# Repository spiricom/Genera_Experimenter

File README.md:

# Genera_H7_rev3
Genera repository for the rev3 boards (summer 2019) STM32H743
test

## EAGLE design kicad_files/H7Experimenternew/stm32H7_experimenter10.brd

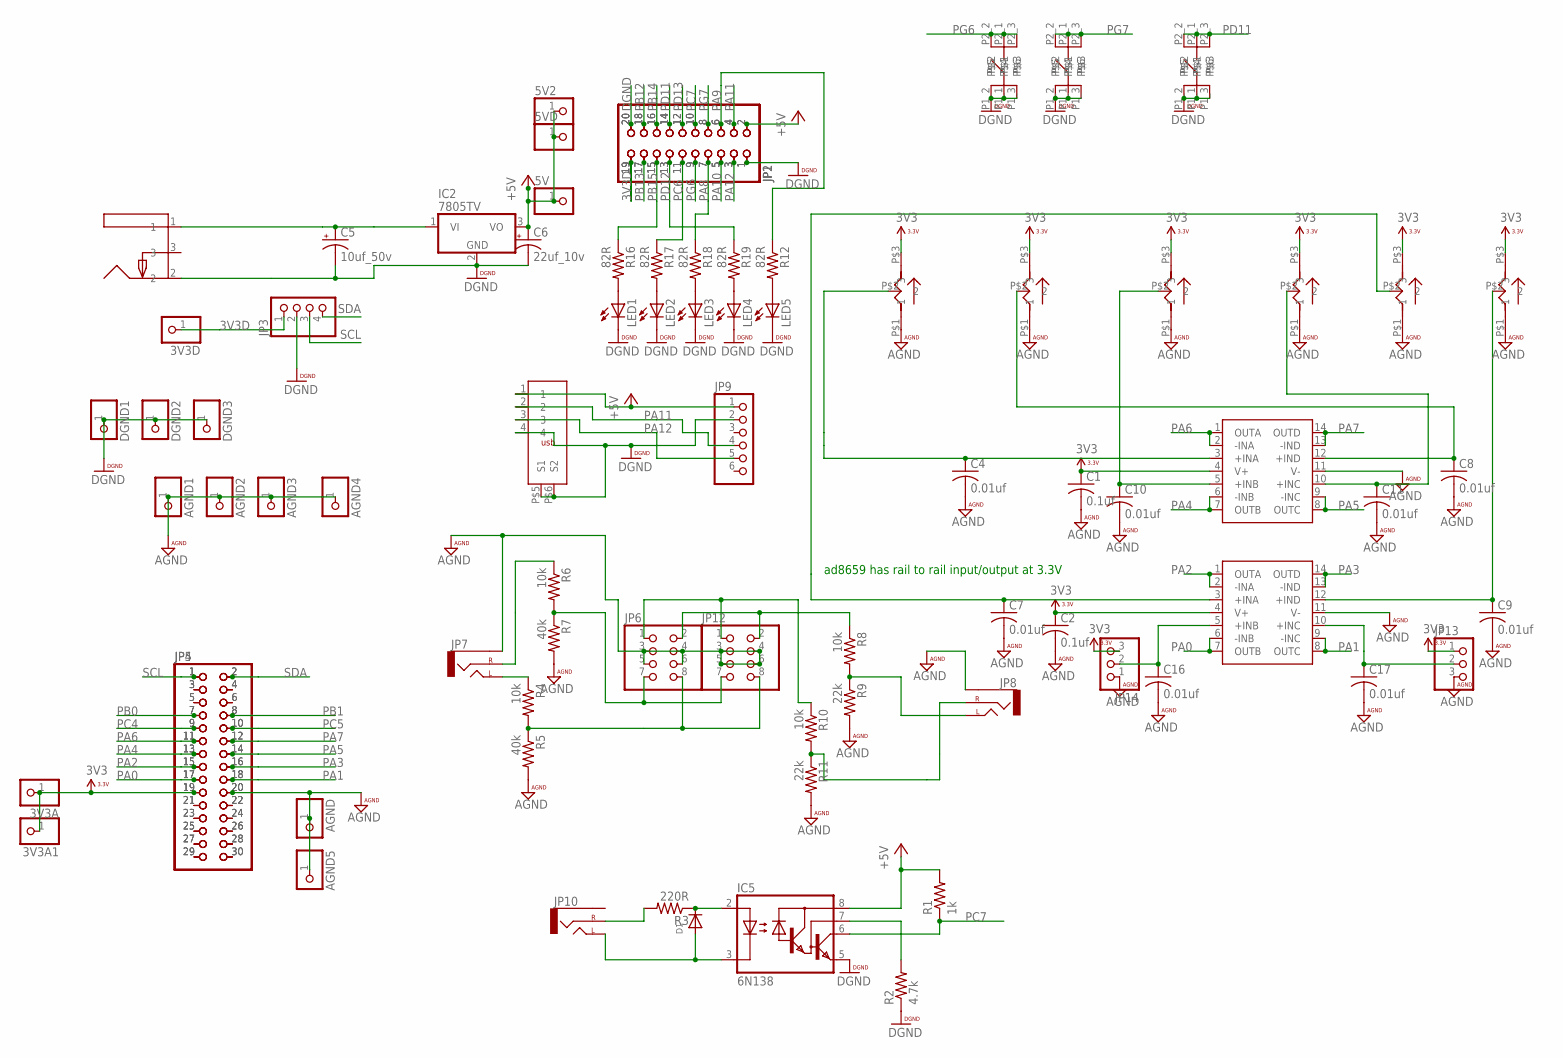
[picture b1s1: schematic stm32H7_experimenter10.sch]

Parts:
3V3A, 3V3A1, 3V3D, 5V, 5V2, 5VD: PINHD-1X1; 1X01; PARTNO *DNP
AGND, AGND1, AGND2, AGND3, AGND4, AGND5: PINHD-1X1; 1X01; PARTNO *DNP
C1, C2: 0.1uf; C025-030X050; PARTNO K104K15X7RF5TL2
C4, C7, C8, C9, C10, C11, C16, C17: 0.01uf; C025-030X050; PARTNO K103K15X7RF5TL2
C5: 10uf_50v; SMC_C; PARTNO 293D106X9035C2TE3
C6: 22uf_10v; SMC_C; PARTNO T491C226K016AT
D1: DIODEDO-1N4148; DO-1N4148; PARTNO 1N4148
DGND1, DGND2, DGND3: PINHD-1X1; 1X01; PARTNO *DNP
IC1, IC3: AD8659; SO14; PARTNO AD8659ARZ-R7
IC2: 7805TV; TO220V; PARTNO VX7805-1000
IC5: 6N138; DIL08; PARTNO 6N138
JP1: PINHD-2X10; 2X10; PARTNO *DNP
JP2: PINHD-2X10; 2X10; PARTNO 67996-120HLF
JP3: PINHD-1X4; 1X04; PARTNO *DNP
JP4: PINHD-2X15; 2X15; PARTNO 67996-130HLF
JP5: PINHD-2X15; 2X15; PARTNO *DNP
JP6: PINHD-2X4; 2X04; PARTNO 67996-108HLF
JP7, JP8, JP10: AUDIO-JACKPTH; AUDIO-JACK; PARTNO SJ1-3525N
JP9: PINHD-1X6; 1X06
JP12: PINHD-2X4; 2X04; PARTNO *DNP
JP13, JP14: PINHD-1X3; 1X03; PARTNO *DNP
LED1, LED2, LED3, LED4, LED5: LED3MM; PARTNO 151031SS04000
P1, P2, P3, P4, P5, P6: RK09SONGHUEI; R0904N; PARTNO *
R1: 1k; 0204/5; PARTNO RNMF14FTC1K00
R2: 4.7k; 0204/5; PARTNO RNMF14FTC4K70
R3: 220R; 0204/5; PARTNO RNMF14FTC220R
R4, R6, R8, R10: 10k; 0204/5; PARTNO RNMF14FTC10K0
R5, R7: 40k; 0204/5; PARTNO RNMF14FTC39K0
R9, R11: 22k; 0204/5; PARTNO RNMF14FTC22K0
R12, R18, R19: 82R; 0204/5; PARTNO RNMF14FTC82R0
R16, R17: 82R; 0204V; PARTNO RNMF14FTC82R0
S1, S2, S3: TL52_PLUS; PARTNO TL52AF160Q
U$1: PJ-058AH_PWR_JACK; PJ-058AH
U$3: USB_292303-1; 292303

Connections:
3V3A: 3V3A.1, 3V3A1.1, C1.1, C2.1, IC1.4 (V+), IC3.4 (V+), JP4.19, JP5.19, JP13.1, JP14.3, P1.P$3 (3), P2.P$3 (3), P3.P$3 (3), P4.P$3 (3), P5.P$3 (3), P6.P$3 (3)
3V3D: 3V3D.1, JP1.19, JP2.19, JP3.1
+5V: 5V.1, 5V2.1, 5VD.1, C6.+, IC2.3 (VO), IC5.8 (VCC), JP1.2, JP2.2, JP9.1, R1.2, U$3.1
AGND: AGND.1, AGND1.1, AGND2.1, AGND3.1, AGND4.1, AGND5.1, C1.2, C2.2, C4.2, C7.2, C8.2, C9.2, C10.2, C11.2, C16.2, C17.2, IC1.11 (V-), IC3.11 (V-), JP4.20, JP5.20, JP6.3, JP6.4, JP6.5, JP6.6, JP7.SLEEVE, JP8.SLEEVE, JP12.3, JP12.4, JP12.5, JP12.6, JP13.3, JP14.1, P1.P$1 (1), P2.P$1 (1), P3.P$1 (1), P4.P$1 (1), P5.P$1 (1), P6.P$1 (1), R5.2, R7.2, R9.2, R11.2
DGND: C5.-, C6.-, DGND1.1, DGND2.1, DGND3.1, IC2.2 (GND), IC5.5 (GND), JP1.1, JP1.20, JP2.1, JP2.20, JP3.2, JP9.2, LED1.K (C), LED2.K (C), LED3.K (C), LED4.K (C), LED5.K (C), R2.1, S1.P1_1, S1.P1_2, S1.P1_3, S2.P1_1, S2.P1_2, S2.P1_3, S3.P1_1, S3.P1_2, S3.P1_3, U$1.2, U$3.4, U$3.P$5 (S1), U$3.P$6 (S2)
unnamed: D1.A, IC5.3 (C), JP10.TIP (LEFT)
unnamed: D1.C, IC5.2 (A), R3.1
unnamed: IC5.7 (VB), R2.2
unnamed: JP10.RING (RIGHT), R3.2
unnamed: C4.1, IC1.3 (+INA), P1.P$2 (2)
unnamed: C8.1, IC1.12 (+IND), P2.P$2 (2)
unnamed: C10.1, IC1.5 (+INB), P3.P$2 (2)
unnamed: C11.1, IC1.10 (+INC), P4.P$2 (2)
unnamed: JP4.3, JP5.3
unnamed: JP4.4, JP5.4
unnamed: JP4.5, JP5.5
unnamed: JP4.6, JP5.6
unnamed: C7.1, IC3.3 (+INA), P5.P$2 (2)
unnamed: C9.1, IC3.12 (+IND), P6.P$2 (2)
unnamed: JP4.21, JP5.21
unnamed: JP4.22, JP5.22
unnamed: C5.+, IC2.1 (VI), U$1.1
unnamed: C16.1, IC3.5 (+INB), JP14.2
unnamed: JP6.8, JP12.8, R4.2, R5.1
unnamed: JP6.7, JP12.7, R6.2, R7.1
unnamed: LED5.A, R12.2
unnamed: JP7.TIP (LEFT), R4.1
unnamed: JP8.TIP (LEFT), R8.2, R9.1
unnamed: C17.1, IC3.10 (+INC), JP13.2
unnamed: JP7.RING (RIGHT), R6.1
unnamed: JP6.2, JP12.2, R8.1
unnamed: JP8.RING (RIGHT), R10.2, R11.1
unnamed: JP6.1, JP12.1, R10.1
unnamed: LED1.A, R16.2
unnamed: LED2.A, R17.2
unnamed: LED3.A, R18.2
unnamed: LED4.A, R19.2
unnamed: JP4.23, JP5.23
unnamed: JP4.24, JP5.24
unnamed: JP4.25, JP5.25
unnamed: JP4.26, JP5.26
unnamed: JP4.27, JP5.27
unnamed: JP4.28, JP5.28
unnamed: JP4.29, JP5.29
unnamed: JP4.30, JP5.30
PA0: IC3.6 (-INB), IC3.7 (OUTB), JP4.17, JP5.17
PA1: IC3.8 (OUTC), IC3.9 (-INC), JP4.18, JP5.18
PA2: IC3.1 (OUTA), IC3.2 (-INA), JP4.15, JP5.15
PA3: IC3.13 (-IND), IC3.14 (OUTD), JP4.16, JP5.16
PA4: IC1.6 (-INB), IC1.7 (OUTB), JP4.13, JP5.13
PA5: IC1.8 (OUTC), IC1.9 (-INC), JP4.14, JP5.14
PA6: IC1.1 (OUTA), IC1.2 (-INA), JP4.11, JP5.11
PA7: IC1.13 (-IND), IC1.14 (OUTD), JP4.12, JP5.12
PA8: JP1.7, JP2.7, R18.1
PA9: JP1.6, JP2.6, R12.1
PA10: JP1.5, JP2.5
PA11: JP1.4, JP2.4, JP9.4, U$3.2
PA12: JP1.3, JP2.3, JP9.5, U$3.3
PB0: JP4.7, JP5.7
PB1: JP4.8, JP5.8
PB12: JP1.18, JP2.18
PB13: JP1.17, JP2.17
PB14: JP1.16, JP2.16
PB15: JP1.15, JP2.15, R16.1
PC4: JP4.9, JP5.9
PC5: JP4.10, JP5.10
PC6: JP1.11, JP2.11, R17.1
PC7: IC5.6 (VO), JP1.10, JP2.10, R1.1
PD11: JP1.14, JP2.14, S3.P2_1, S3.P2_2, S3.P2_3
PD12: JP1.13, JP2.13, R19.1
PD13: JP1.12, JP2.12
PG6: JP1.9, JP2.9, S1.P2_1, S1.P2_2, S1.P2_3
PG7: JP1.8, JP2.8, S2.P2_1, S2.P2_2, S2.P2_3
SCL: JP3.3, JP4.1, JP5.1
SDA: JP3.4, JP4.2, JP5.2

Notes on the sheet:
ad8659 has rail to rail input/output at 3.3V

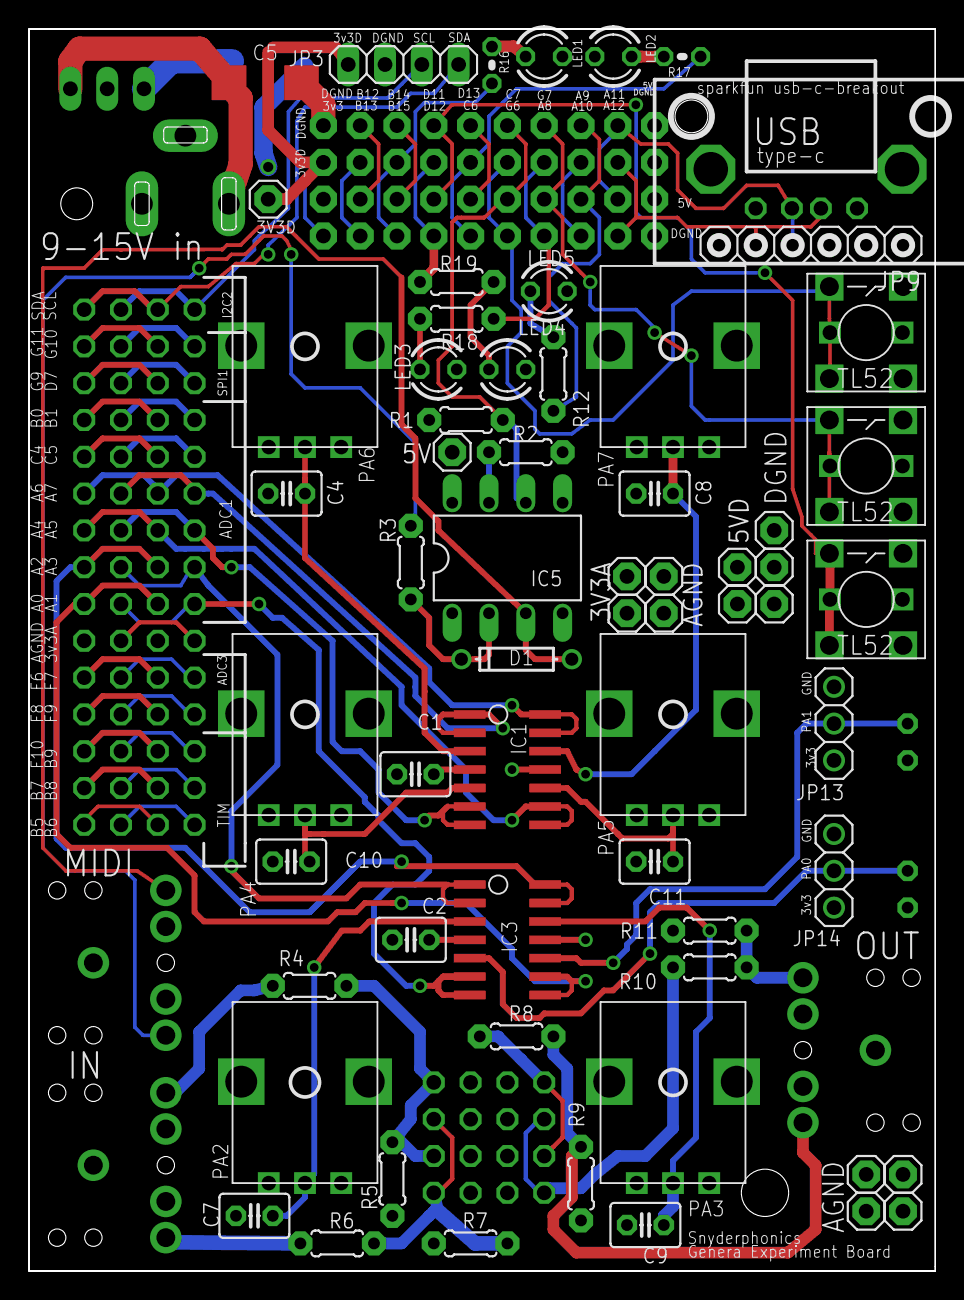
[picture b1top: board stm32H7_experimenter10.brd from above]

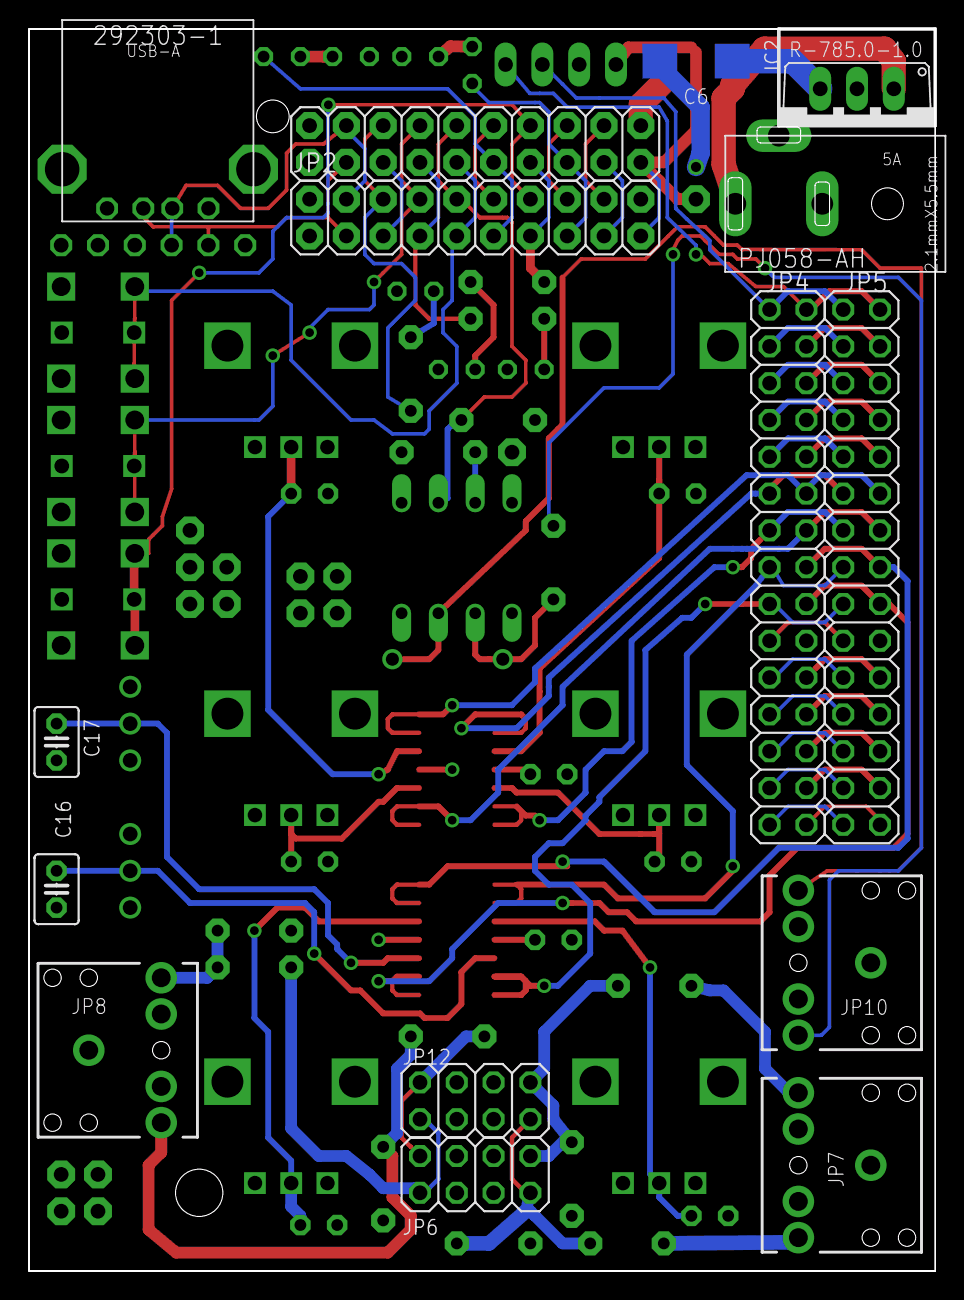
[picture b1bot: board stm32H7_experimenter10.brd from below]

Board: 6 copper layers, 62.5 x 85.7 mm, 77 parts (15 on the bottom side), 75 nets.

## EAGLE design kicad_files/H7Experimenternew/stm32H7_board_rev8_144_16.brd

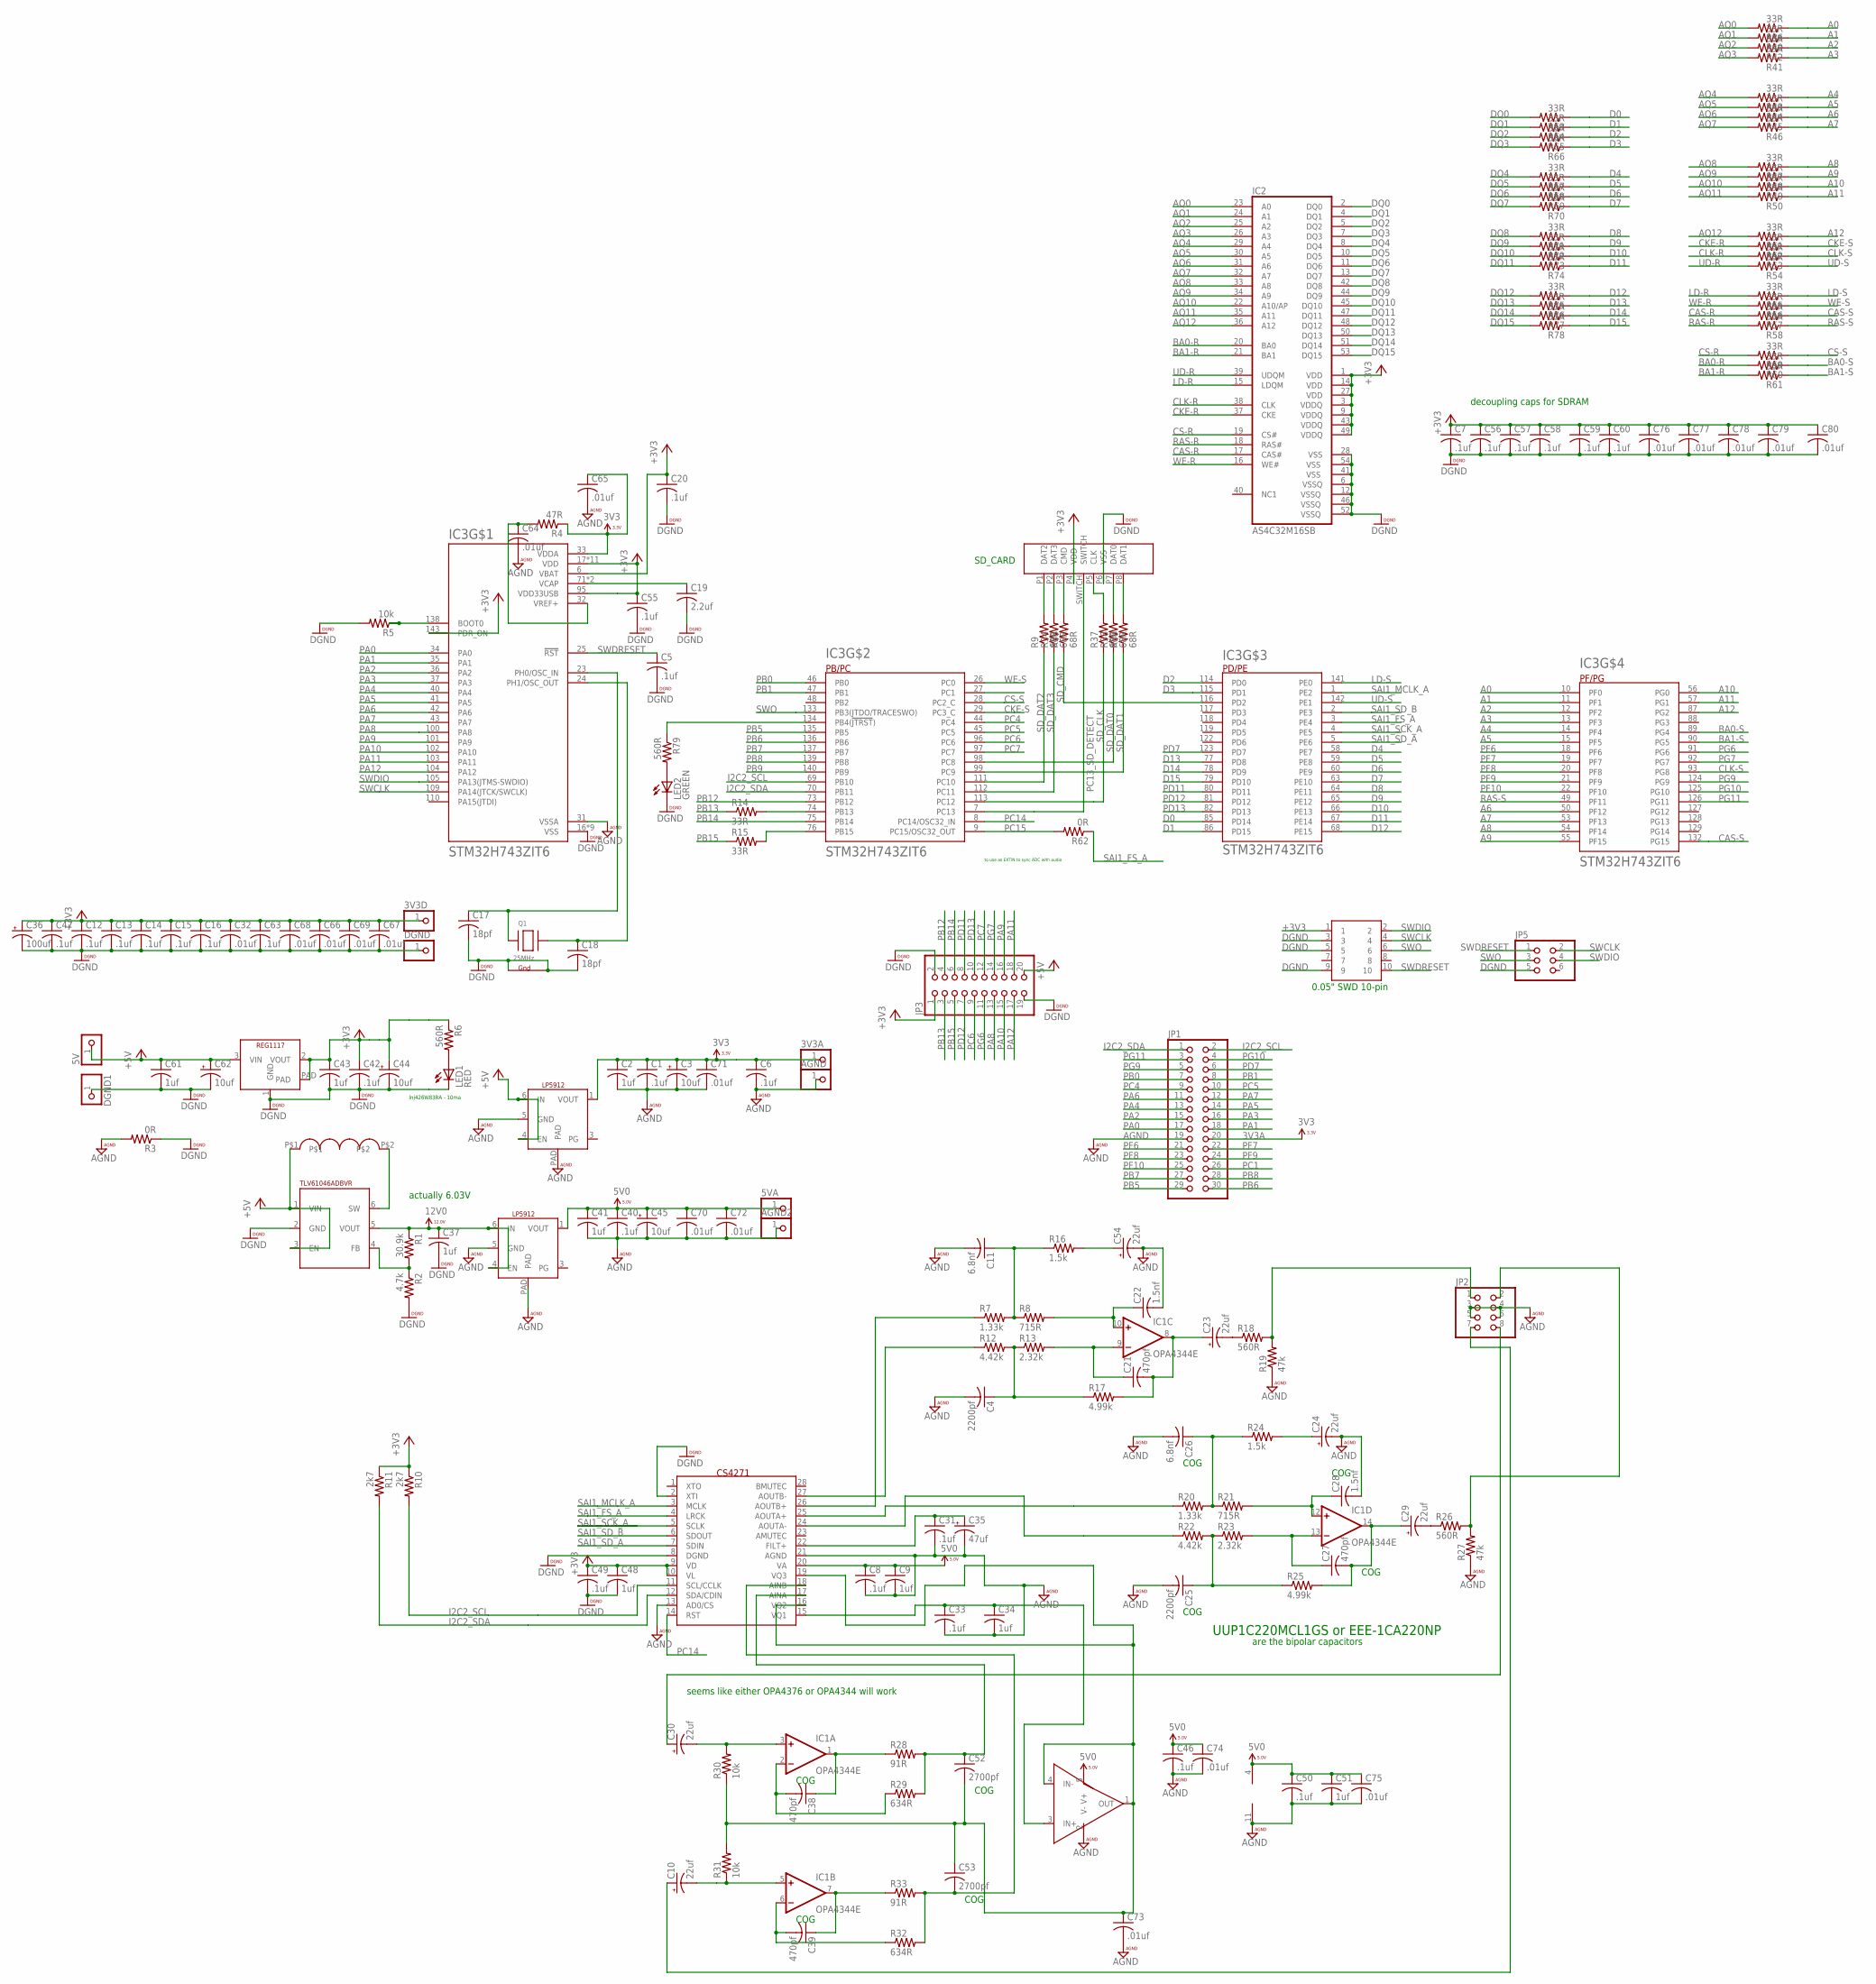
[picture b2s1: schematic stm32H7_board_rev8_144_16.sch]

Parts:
3V3A, 3V3D, 5V, 5VA: PINHD-1X1; 1X01; PARTNO *DNP
AGND, AGND2: PINHD-1X1; 1X01; PARTNO *DNP
C1, C8, C31, C33, C40, C42, C46, C49, C50: .1uf; C0603; PARTNO CC0603KRX7R8BB104
C2, C9, C34, C37, C41, C43, C48, C51, C61: 1uf; C1206; PARTNO C3216X7R1E105K085AA
C3, C44, C45, C62: 10uf; SMC_B; PARTNO TAJB106K025RNJ
C4, C25: 2200pf; C0603; PARTNO CC0603JRNPO9BN221
C5, C6, C7, C12, C13, C14, C15, C16, C20, C47, C55, C56, C57, C58, C59, C60, C63: .1uf; C0402; PARTNO CC0402KRX7R8BB104
C10, C23, C24, C29, C30, C54: 22uf; PANASONIC_D; PARTNO EEE-1CA220NP
C11, C26: 6.8nf; C0603; PARTNO C0603C682J5GACTU
C17, C18: 18pf; C0603; PARTNO CL10C180JB8NNNC
C19: 2.2uf; C1206; PARTNO T491A225K020AT
C21, C27, C38, C39: 470pf; C0603; PARTNO CC0603JRNPO9BN471
C22, C28: 1.5nf; C0603; PARTNO C0603C152J5GACTU
C32, C64, C65: .01uf; C0402; PARTNO CC0402KRX7R8BB103
C35: 47uf; PANASONIC_D; PARTNO EEE-1CA470AP
C36: 100uf; PANASONIC_E; PARTNO EEE-1CA101AP
C52, C53: 2700pf; C0603; PARTNO C0603C272J5GACTU
C66, C67, C68, C69, C70, C71, C72, C73, C74, C75, C76, C77, C78, C79, C80: .01uf; C0201; PARTNO TMK063B7103KP-F
DGND, DGND1: PINHD-1X1; 1X01; PARTNO *DNP
IC1: OPA4344E; TSSOP14; PARTNO ADA4807-4ARUZ-R7
IC2: AS4C32M16SB; TSOP54; PARTNO AS4C16M16SA-7TCN
IC3: STM32H743ZIT6; QFP50P2200X2200X160-144N; PARTNO STM32H743ZIT6
IC4: REG1117; SOT223; PARTNO LM1117IMPX-3.3/NOPB
IC5: CS4271; TSSOP28; PARTNO CS4271-CZZ
IC6: TLV170; SOT23-5L; PARTNO TLV170IDBVT
IC7: TLV61046ADBVR; SOT23-6; PARTNO TLV61046ADBVR
IC8: LP5912; 6-WSON; PARTNO LP5912-5.0DRVR
IC9: LP5912; 6-WSON; PARTNO LP5912-3.3DRVT
JP1: PINHD-2X15; 2X15; PARTNO 76342-315LF
JP2: PINHD-2X4; 2X04; PARTNO 76342-304LF
JP3: PINHD-2X10; 2X10; PARTNO 76342-310LF
JP5: PINHD-2X3; 2X03; PARTNO *DNP
L1: 74438336100; 1212; PARTNO 74438336100
LED1: RED; CHIP-LED0603; PARTNO 5973006507F
LED2: GREEN; CHIP-LED0603; PARTNO 5973506507F
Q1: 25MHz; NX3225; PARTNO 7M-25.000MAAJ-T
R1: 30.9k; R0603; PARTNO RT0603BRD0730K9L
R2: 4.7k; R0603; PARTNO CRCW06034K70FKEAHP
R3, R62: 0R; R0603; PARTNO RCS06030000Z0EA
R4: 47R; R0603; PARTNO ESR03EZPJ470
R5: 10k; R0402; PARTNO RC0402FR-0710KL
R6, R18, R26, R79: 560R; R0603; PARTNO ESR03EZPF5600
R7, R20: 1.33k; R0603; PARTNO RT0603BRD071K33L
R8, R21: 715R; R0603; PARTNO RC0603FR-07715RL
R9, R34, R35, R37, R38, R39: 68R; R0201; PARTNO RC0201FR-0768RL
R10, R11: 2k7; R0603; PARTNO RT0603BRD072K7L
R12, R22: 4.42k; R0603; PARTNO RT0603BRD074K42L
R13, R23: 2.32k; R0603; PARTNO RT0603BRD072K32L
R14, R15: 33R; R0402; PARTNO RC0402FR-0733RL
R16, R24: 1.5k; R0603; PARTNO ESR03EZPJ152
R17, R25: 4.99k; R0603; PARTNO RT0603BRD074K99L
R19, R27: 47k; R0603; PARTNO ESR03EZPJ473
R28, R33: 91R; R0603; PARTNO RC0603JR-0791RL
R29, R32: 634R; R0603; PARTNO RC0603FR-07634RL
R30, R31: 10k; R0603; PARTNO ESR03EZPF1002
R36, R40, R41, R42, R43, R44, R45, R46, R47, R48, R49, R50, R51, R52, R53, R54, R55, R56, R57, R58, R59, R60, R61, R63, R64, R65, R66, R67, R68, R69, R70, R71, R72, R73, R74, R75, R76, R77, R78: 33R; R0201; PARTNO RC0201FR-0733RL
X1: 1050270001_SD_CARD_CONNECTOR; 1050270001; PARTNO 1050270001
X2: 3221-10-0300-00; PARTNO 3221-10-0300-00

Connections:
3V3A: 3V3A.1, C1.1, C2.1, C3.+, C6.1, C65.1, C71.1, IC3.33 (VDDA), IC9.1 (VOUT), JP1.20, R4.1
5V0: 5VA.1, C8.1, C9.1, C40.1, C41.1, C45.+, C46.1, C50.1, C51.1, C70.1, C72.1, C74.1, C75.1, IC1.4 (V+), IC5.20 (VA), IC6.5 (V+), IC8.1 (VOUT)
12V0: C37.1, IC7.5 (VOUT), IC8.4 (EN), IC8.6 (IN), R1.1
+3V3: 3V3D.1, C7.1, C12.1, C13.1, C14.1, C15.1, C16.1, C20.1, C32.1, C36.+, C42.1, C43.1, C44.+, C47.1, C48.1, C49.1, C55.1, C56.1, C57.1, C58.1, C59.1, C60.1, C63.1, C66.1, C67.1, C68.1, C69.1, C76.1, C77.1, C78.1, C79.1, C80.1, IC2.1 (VDD), IC2.3 (VDDQ), IC2.9 (VDDQ), IC2.14 (VDD), IC2.27 (VDD), IC2.43 (VDDQ), IC2.49 (VDDQ), IC3.6 (VBAT), IC3.17 (VDD), IC3.30 (VDD), IC3.39 (VDD), IC3.52 (VDD), IC3.62 (VDD), IC3.72 (VDD), IC3.84 (VDD), IC3.95 (VDD33USB), IC3.108 (VDD), IC3.121 (VDD), IC3.131 (VDD), IC3.143 (PDR_ON), IC3.144 (VDD), IC4.2 (VOUT), IC4.PAD, IC5.9 (VD), IC5.10 (VL), JP3.1, R6.1, R10.1, R11.1, X1.P4 (VDD), X2.1
+5V: 5V.1, C61.1, C62.+, IC4.3 (VIN), IC7.1 (VIN), IC7.3 (EN), IC9.4 (EN), IC9.6 (IN), JP3.20, L1.P$1
A0: IC3.10 (PF0), R36.1
A1: IC3.11 (PF1), R40.1
A2: IC3.12 (PF2), R42.1
A3: IC3.13 (PF3), R41.1
A4: IC3.14 (PF4), R43.1
A5: IC3.15 (PF5), R44.1
A6: IC3.50 (PF12), R45.1
A7: IC3.53 (PF13), R46.1
A8: IC3.54 (PF14), R47.1
A9: IC3.55 (PF15), R48.1
A10: IC3.56 (PG0), R49.1
A11: IC3.57 (PG1), R50.1
A12: IC3.87 (PG2), R51.1
AGND: AGND.1, AGND2.1, C1.2, C2.2, C3.-, C4.2, C6.2, C8.2, C9.2, C11.2, C22.2, C24.-, C25.2, C26.2, C28.2, C31.2, C33.2, C34.2, C35.-, C40.2, C41.2, C45.-, C46.2, C50.2, C51.2, C54.-, C64.2, C65.2, C70.2, C71.2, C72.2, C73.2, C74.2, C75.2, IC1.11 (V-), IC3.31 (VSSA), IC5.13 (AD0/CS), IC5.21 (AGND), IC6.2 (V-), IC8.5 (GND), IC8.PAD, IC9.5 (GND), IC9.PAD, JP1.19, JP2.3, JP2.4, JP2.5, JP2.6, R3.2, R19.1, R27.1
AQ0: IC2.23 (A0), R36.2
AQ1: IC2.24 (A1), R40.2
AQ2: IC2.25 (A2), R42.2
AQ3: IC2.26 (A3), R41.2
AQ4: IC2.29 (A4), R43.2
AQ5: IC2.30 (A5), R44.2
AQ6: IC2.31 (A6), R45.2
AQ7: IC2.32 (A7), R46.2
AQ8: IC2.33 (A8), R47.2
AQ9: IC2.34 (A9), R48.2
AQ10: IC2.22 (A10/AP), R49.2
AQ11: IC2.35 (A11), R50.2
AQ12: IC2.36 (A12), R51.2
BA0-R: IC2.20 (BA0), R60.2
BA0-S: IC3.89 (PG4), R60.1
BA1-R: IC2.21 (BA1), R61.2
BA1-S: IC3.90 (PG5), R61.1
CAS-R: IC2.17 (CAS#), R57.2
CAS-S: IC3.132 (PG15), R57.1
CKE-R: IC2.37 (CKE), R52.2
CKE-S: IC3.29 (PC3_C), R52.1
CLK-R: IC2.38 (CLK), R53.2
CLK-S: IC3.93 (PG8), R53.1
CS-R: IC2.19 (CS#), R59.2
CS-S: IC3.28 (PC2_C), R59.1
D0: IC3.85 (PD14), R63.1
D1: IC3.86 (PD15), R64.1
D2: IC3.114 (PD0), R65.1
D3: IC3.115 (PD1), R66.1
D4: IC3.58 (PE7), R67.1
D5: IC3.59 (PE8), R68.1
D6: IC3.60 (PE9), R69.1
D7: IC3.63 (PE10), R70.1
D8: IC3.64 (PE11), R71.1
D9: IC3.65 (PE12), R72.1
D10: IC3.66 (PE13), R73.1
D11: IC3.67 (PE14), R74.1
D12: IC3.68 (PE15), R75.1
D13: IC3.77 (PD8), R76.1
D14: IC3.78 (PD9), R77.1
D15: IC3.79 (PD10), R78.1
DGND: C5.2, C7.2, C12.2, C13.2, C14.2, C15.2, C16.2, C17.2, C18.2, C19.2, C20.2, C32.2, C36.-, C37.2, C42.2, C43.2, C44.-, C47.2, C48.2, C49.2, C55.2, C56.2, C57.2, C58.2, C59.2, C60.2, C61.2, C62.-, C63.2, C66.2, C67.2, C68.2, C69.2, C76.2, C77.2, C78.2, C79.2, C80.2, DGND.1, DGND1.1, IC2.6 (VSSQ), IC2.12 (VSSQ), IC2.28 (VSS), IC2.41 (VSS), IC2.46 (VSSQ), IC2.52 (VSSQ), IC2.54 (VSS), IC3.16 (VSS), IC3.38 (VSS), IC3.51 (VSS), IC3.61 (VSS), IC3.83 (VSS), IC3.94 (VSS), IC3.107 (VSS), IC3.120 (VSS), IC3.130 (VSS), IC4.1 (GND), IC5.2 (XTI), IC5.8 (DGND), IC7.2 (GND), JP3.2, JP3.19, JP5.5, LED1.C, LED2.C, Q1.2 (G2), Q1.4 (G1), R2.2, R3.1, R5.2, X1.P6 (VSS), X2.3, X2.5, X2.9
DQ0: IC2.2 (DQ0), R63.2
DQ1: IC2.4 (DQ1), R64.2
DQ2: IC2.5 (DQ2), R65.2
DQ3: IC2.7 (DQ3), R66.2
DQ4: IC2.8 (DQ4), R67.2
DQ5: IC2.10 (DQ5), R68.2
DQ6: IC2.11 (DQ6), R69.2
DQ7: IC2.13 (DQ7), R70.2
DQ8: IC2.42 (DQ8), R71.2
DQ9: IC2.44 (DQ9), R72.2
DQ10: IC2.45 (DQ10), R73.2
DQ11: IC2.47 (DQ11), R74.2
DQ12: IC2.48 (DQ12), R75.2
DQ13: IC2.50 (DQ13), R76.2
DQ14: IC2.51 (DQ14), R77.2
DQ15: IC2.53 (DQ15), R78.2
FB: IC7.4 (FB), R1.2, R2.1
FILT_A: C31.1, C35.+, IC5.22 (FILT+)
I2C2_SCL: IC3.69 (PB10), IC5.11 (SCL/CCLK), JP1.2, R10.2
I2C2_SDA: IC3.70 (PB11), IC5.12 (SDA/CDIN), JP1.1, R11.2
LD-R: IC2.15 (LDQM), R55.2
LD-S: IC3.141 (PE0), R55.1
unnamed: IC5.24 (AOUTA-), R22.1
unnamed: IC3.74 (PB13), R14.2
unnamed: IC3.76 (PB15), R15.2
unnamed: LED2.A, R79.2
unnamed: IC3.134 (PB4(!JTRST!)), R79.1
unnamed: C39.1, IC1.7 (OUT), R33.1
unnamed: R35.2, X1.P3 (CMD)
unnamed: R34.2, X1.P2 (DAT3)
unnamed: R9.2, X1.P1 (DAT2)
unnamed: R39.2, X1.P8 (DAT1)
unnamed: C11.1, R7.2, R8.1, R16.1
unnamed: R38.2, X1.P7 (DAT0)
unnamed: R37.2, X1.P5 (CLK)
unnamed: IC3.138 (BOOT0), R5.1
unnamed: LED1.A, R6.2
unnamed: IC5.25 (AOUTA+), R20.1
unnamed: IC5.26 (AOUTB+), R7.1
unnamed: C22.1, IC1.10 (+IN), R8.2
unnamed: C21.1, IC1.9 (-IN), R13.2
unnamed: IC5.27 (AOUTB-), R12.1
unnamed: JP2.1, R18.2, R19.2
unnamed: C23.-, R18.1
unnamed: C4.1, R12.2, R13.1, R17.1
unnamed: C21.2, C23.+, IC1.8 (OUT), R17.2
unnamed: C54.+, R16.2
unnamed: C28.1, IC1.12 (+IN), R21.2
unnamed: C27.1, IC1.13 (-IN), R23.2
unnamed: JP2.2, R26.2, R27.2
unnamed: C29.-, R26.1
unnamed: C25.1, R22.2, R23.1, R25.1
unnamed: C27.2, C29.+, IC1.14 (OUT), R25.2
unnamed: C26.1, R20.2, R21.1, R24.1
unnamed: C24.+, R24.2
unnamed: C52.2, C53.1, C73.1, IC5.16 (VQ2), IC5.19 (VQ3), IC6.1 (OUT), IC6.4 (IN-), R30.1, R31.2
unnamed: C30.+, JP2.8
unnamed: C10.+, JP2.7
unnamed: C30.-, IC1.3 (+IN), R30.2
unnamed: C10.-, IC1.5 (+IN), R31.1
unnamed: C38.2, IC1.2 (-IN), R29.1
unnamed: C38.1, IC1.1 (OUT), R28.1
unnamed: C39.2, IC1.6 (-IN), R32.1
unnamed: C52.1, IC5.17 (AINA), R28.2, R29.2
unnamed: C53.2, IC5.18 (AINB), R32.2, R33.2
OSC1: C17.1, IC3.23 (PH0/OSC_IN), Q1.1 (X1)
OSC2: C18.1, IC3.24 (PH1/OSC_OUT), Q1.3 (X2)
PA0: IC3.34 (PA0), JP1.17
PA1: IC3.35 (PA1), JP1.18
PA2: IC3.36 (PA2), JP1.15
PA3: IC3.37 (PA3), JP1.16
PA4: IC3.40 (PA4), JP1.13
PA5: IC3.41 (PA5), JP1.14
PA6: IC3.42 (PA6), JP1.11
PA7: IC3.43 (PA7), JP1.12
PA8: IC3.100 (PA8), JP3.13
PA9: IC3.101 (PA9), JP3.16
PA10: IC3.102 (PA10), JP3.15
PA11: IC3.103 (PA11), JP3.18
PA12: IC3.104 (PA12), JP3.17
PB0: IC3.46 (PB0), JP1.7
PB1: IC3.47 (PB1), JP1.8
PB5: IC3.135 (PB5), JP1.29
PB6: IC3.136 (PB6), JP1.30
PB7: IC3.137 (PB7), JP1.27
PB8: IC3.139 (PB8), JP1.28
PB9: IC3.140 (PB9)
PB12: IC3.73 (PB12), JP3.4
PB13: JP3.3, R14.1
PB14: IC3.75 (PB14), JP3.6
PB15: JP3.5, R15.1
PC1: IC3.27 (PC1), JP1.26
PC4: IC3.44 (PC4), JP1.9
PC5: IC3.45 (PC5), JP1.10
PC6: IC3.96 (PC6), JP3.9
PC7: IC3.97 (PC7), JP3.12
PC13_SD_DETECT: IC3.7 (PC13), X1.SWITCH
PC14: IC3.8 (PC14/OSC32_IN), IC5.14 (RST)
PC15: IC3.9 (PC15/OSC32_OUT), R62.2
PD7: IC3.123 (PD7), JP1.6
PD11: IC3.80 (PD11), JP3.8
PD12: IC3.81 (PD12), JP3.7
PD13: IC3.82 (PD13), JP3.10
PF6: IC3.18 (PF6), JP1.21
PF7: IC3.19 (PF7), JP1.22
PF8: IC3.20 (PF8), JP1.23
PF9: IC3.21 (PF9), JP1.24
PF10: IC3.22 (PF10), JP1.25
PG6: IC3.91 (PG6), JP3.11
PG7: IC3.92 (PG7), JP3.14
PG9: IC3.124 (PG9), JP1.5
PG10: IC3.125 (PG10), JP1.4
PG11: IC3.126 (PG11), JP1.3
RAS-R: IC2.18 (RAS#), R58.2
RAS-S: IC3.49 (PF11), R58.1
SAI1_FS_A: IC3.3 (PE4), IC5.4 (LRCK), R62.1
SAI1_MCLK_A: IC3.1 (PE2), IC5.3 (MCLK)
SAI1_SCK_A: IC3.4 (PE5), IC5.5 (SCLK)
SAI1_SD_A: IC3.5 (PE6), IC5.7 (SDIN)
SAI1_SD_B: IC3.2 (PE3), IC5.6 (SDOUT)
SD_CLK: IC3.113 (PC12), R37.1
SD_CMD: IC3.116 (PD2), R35.1
SD_DAT0: IC3.98 (PC8), R38.1
SD_DAT1: IC3.99 (PC9), R39.1
SD_DAT2: IC3.111 (PC10), R9.1
SD_DAT3: IC3.112 (PC11), R34.1
SW: IC7.6 (SW), L1.P$2
SWCLK: IC3.109 (PA14(JTCK/SWCLK)), JP5.2, X2.4
SWDIO: IC3.105 (PA13(JTMS-SWDIO)), JP5.4, X2.2
SWDRESET: C5.1, IC3.25 (!RST), JP5.1, X2.10
SWO: IC3.133 (PB3(JTDO/TRACESWO)), JP5.3, X2.6
UD-R: IC2.39 (UDQM), R54.2
UD-S: IC3.142 (PE1), R54.1
VCAP: C19.1, IC3.71 (VCAP), IC3.106 (VCAP)
VQ: C33.1, C34.1, IC5.15 (VQ1), IC6.3 (IN+)
VREF: C64.1, IC3.32 (VREF+), R4.2
WE-R: IC2.16 (WE#), R56.2
WE-S: IC3.26 (PC0), R56.1

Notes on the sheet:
lnj426W83RA - 10ma
actually 6.03V
SD_CARD
UUP1C220MCL1GS or EEE-1CA220NP
decoupling caps for SDRAM
COG
seems like either OPA4376 or OPA4344 will work
are the bipolar capacitors
to use as EXTIN to sync ADC with audio
0.05" SWD 10-pin

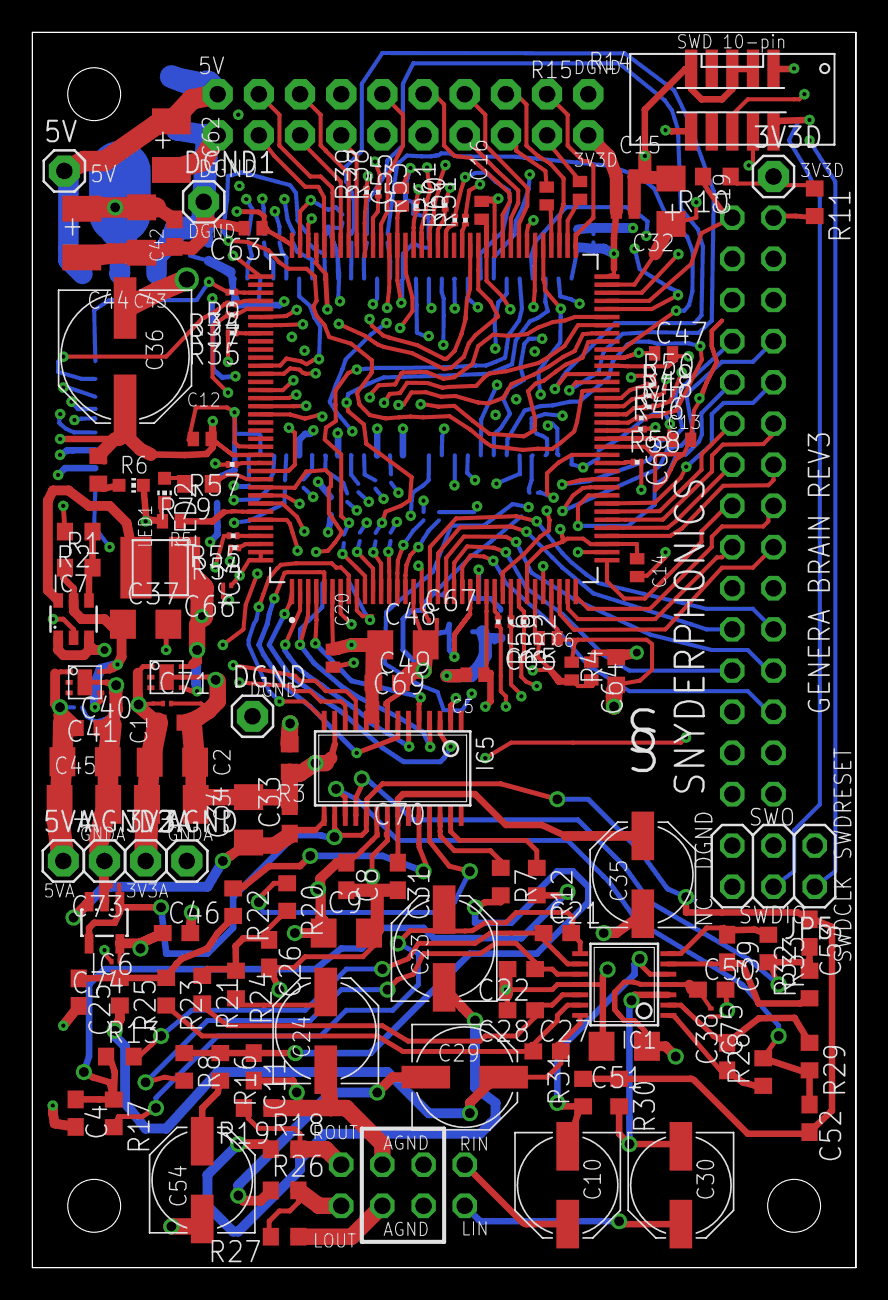
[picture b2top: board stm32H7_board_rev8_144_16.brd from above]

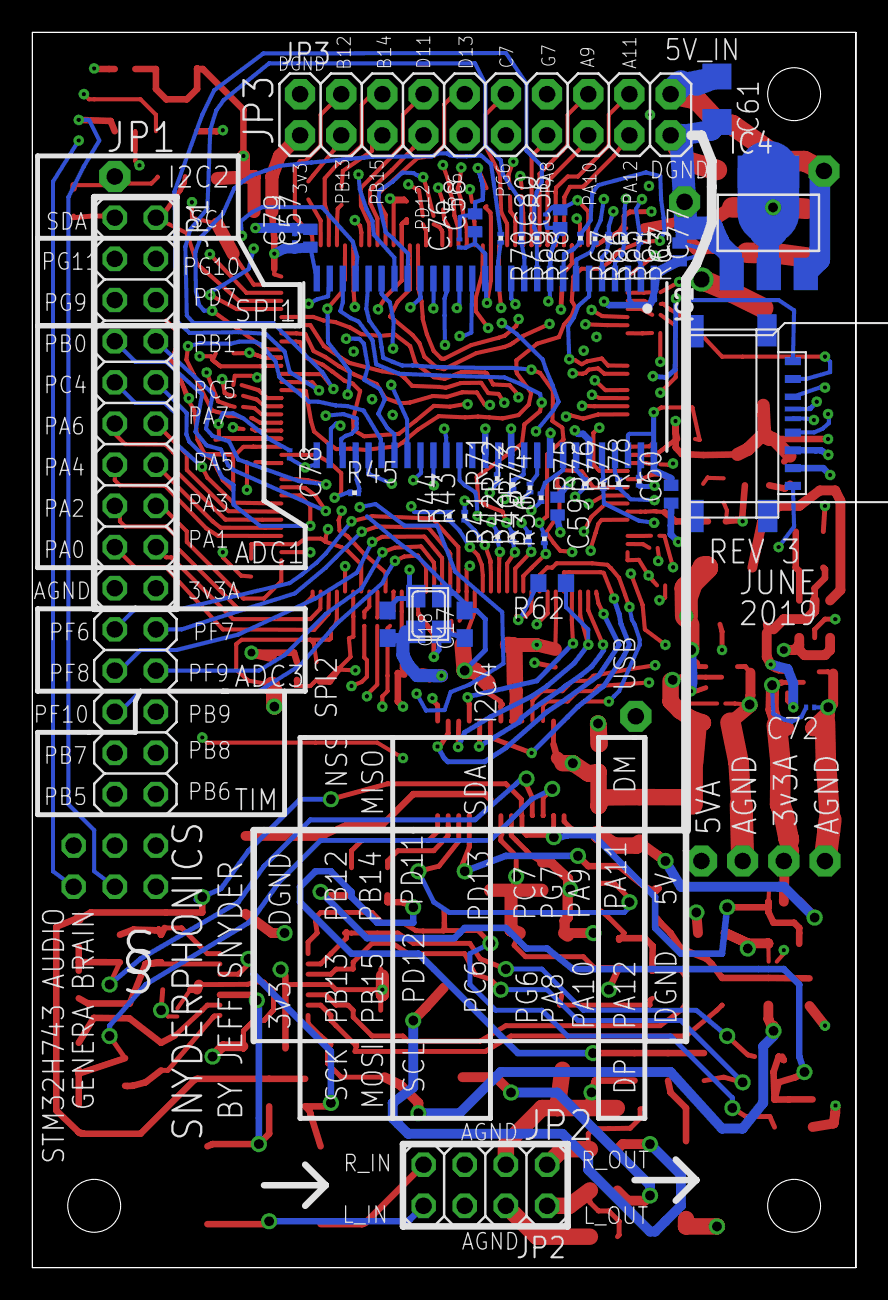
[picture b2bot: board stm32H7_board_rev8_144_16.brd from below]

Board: 6 copper layers, 50.8 x 76.2 mm, 186 parts (46 on the bottom side), 198 nets.

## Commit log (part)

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2020-02-20 updating
2020-03-07 fixed issues with build and broken sw4stm config file
2020-03-07 added mempools to example
2020-03-07 fixed linker file to allow for SDRAM access
2020-03-21 added SPI
2020-03-22 removed unnecessary HAL peripherals, added string fret measurements roughly
2020-03-24 working electrobass makes sound but needs better attack detection
2020-03-26 working attack detector
2020-03-26 slight tweak to reduce mistriggers
2020-04-20 electrobass update;
2020-04-20 added usb midi functionality"
2020-04-23 added vadim zavalishin filters to have high and low shelf, and also saturation
2020-04-23 finished mackie-style eq example using the new Vadim Zavalashin filters. It works! Overloads when boosting highs, but thats probably because the source is white noise with more energy in the upper fr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
2020-04-23 filter test example
2020-06-20 got 3 ADC input channels syncronized with audio frame and samples. They can be used as audio inputs without distortion
2020-06-21 working example that detects which sensor was closest to strike based on oversampled time difference
2020-06-23 migrated to cubeide
2020-06-23 migrated to cubeide and fixed some things
2020-06-25 testing
2020-07-09 edited lots of things, somewht working pluck detection in adc callback, simple monophonic handling
2020-07-10 decent attack detection, currently trying to work on logging to SD card
2020-07-11 got data logging working up to about 50000 bytes. Need to extend beyond that by buffering and sending in chunks or by using SDRAM as temporary storage.
2020-07-27 code to record full sensor data from the electrobass and store it to an SD card for analysis
2020-08-25 updating electrobass
2020-08-30 simple distortion 192k
2020-08-31 distortion 192k example
2020-08-31 cleaned up cycle counter cruft
2020-08-31 updated code to reflect new LEAF changes
2020-08-31 added comment to explain interface;
2020-08-31 newer version with 2X oversampling of all saturation and no saturation in filters
2020-08-31 adjusted ranges of controls for better filtering
2020-08-31 moved comment
2020-09-01 version of filterbank
2020-09-02 pushing current version
2020-09-03 working version that reads a file named s.wav from SD card and plays it back looping.
2020-09-06 added code to allow parsing of broadcast wav files, which previously broke it. Still havent figured out how to handle multichannel files on the reading end
2020-09-06 fixed wave.c to properly read stereo files and read much more quickly by using a large scratch buffer and loading the whole sample data at once rather than tons of tiny sd card reads
2020-09-08 version where the genera takes two triggers in on the audio inputs and sends out two different samples on the output channels
2020-09-09 trying IDMA version of sdmmc
2020-09-10 quite good sample playback happening. Tested using SDMMC IDMA and it was slower because I couldnt use DTCMRAM. Went back to polling. Found tricky bug in the tSampler object that also explains weirdne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
2020-09-10 updated leaf
2020-09-11 added angies code as a leaf object, tested and working with pluck detection but not tested using amplitude information
2020-09-12 working electrobass
2020-11-15 current SD card code
2026-04-15 current state
2026-04-15 updated hal
2026-04-15 replaced with Electrosteel audio version
2026-04-15 errors during build but has electrosteel code
2026-06-11 Fixed bug, updated LEAF
    yeah
2026-06-11 test
2026-06-11 Small bugfix, added .gitignore
    changed uint to uint32_t for newer C versions
2026-06-11 Updated to new LEAF version
2026-06-11 attempted to add submodule reference to new leaf
2026-06-11 Better .gitignore attempt
2026-06-11 removed settings in gitignore
2026-06-11 more gitignore fixes
2026-06-11 More .gitignore fixes
2026-06-11 another
2026-06-11 final gitignore fix?
2026-06-11 another one
2026-06-11 unignoring .cproject
    Seems removing the .cproject file to get rid of the file directory reference to my own computer was a bad idea.
    Changed the leaf submodule directory to reference the workspace instead of my C drive, which should make it universal.
2026-06-11 One more undo
    Removed settings from the .gitignore.
    Not sure if the settings folder is auto-generated upon opening a project, or how system-specific the settings are.
2026-06-18 added kicad file

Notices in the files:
parts and their libraries:
SparkFun-Connectors: Licensing: Creative Commons ShareAlike 4.0 International - https://creativecommons.org/licenses/by-sa/4.0
PatternAgents-Beautify: License : http://creativecommons.org/licenses/by-sa/3.0
(Creative Commons 3.0)
